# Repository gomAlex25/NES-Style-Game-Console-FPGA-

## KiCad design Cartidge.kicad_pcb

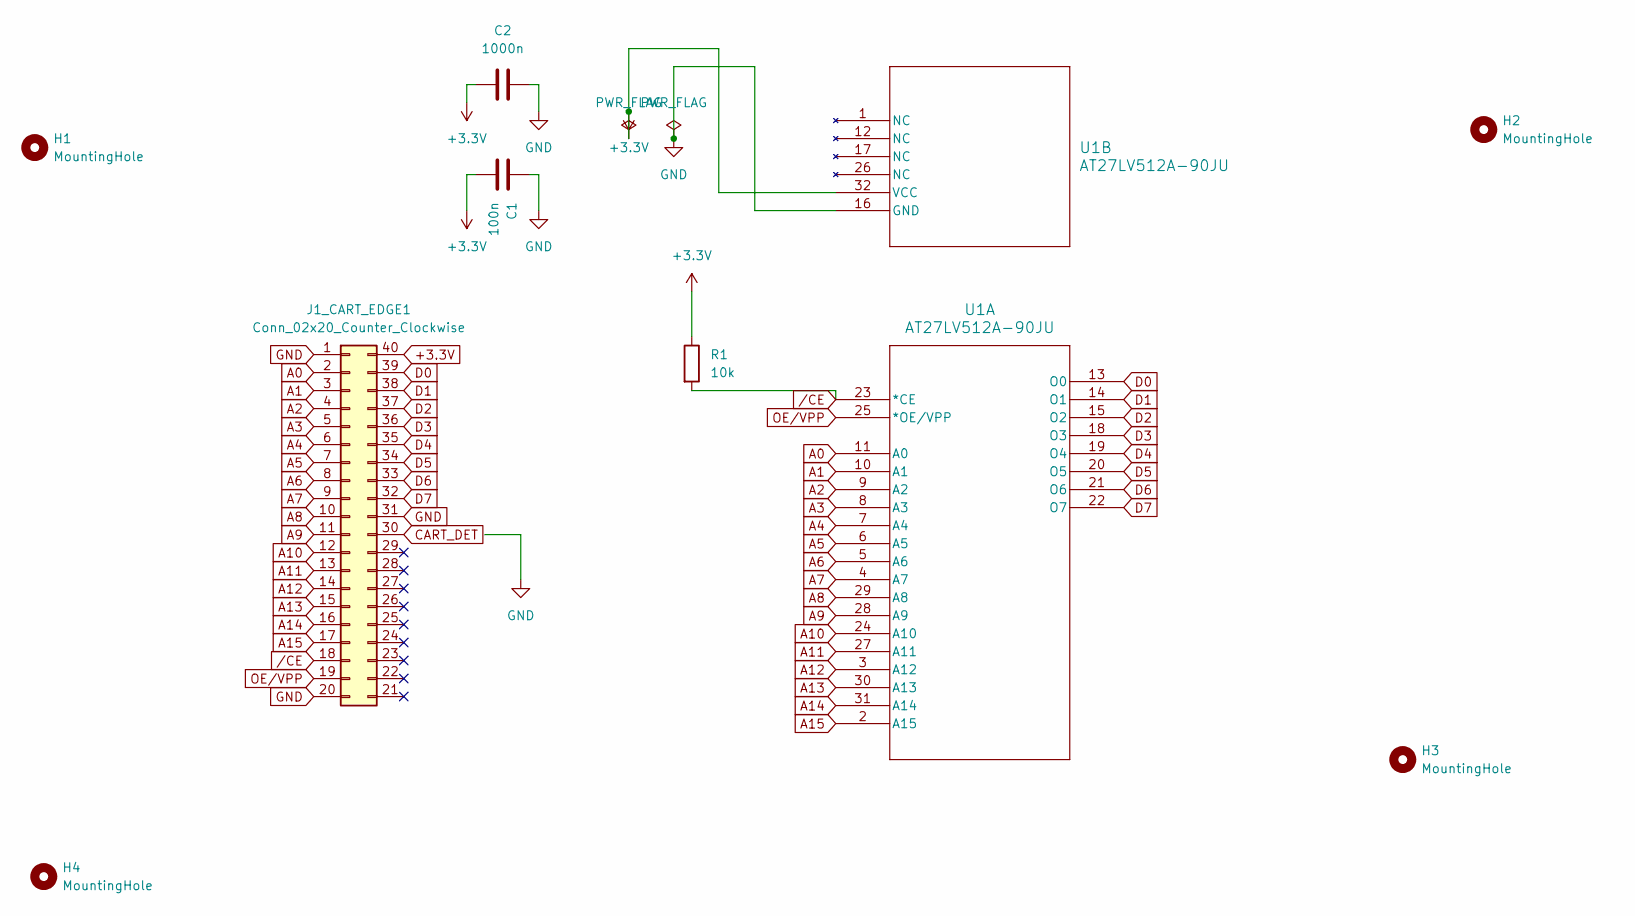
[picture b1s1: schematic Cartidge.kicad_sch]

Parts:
C1: 100n; C_Axial_L3.8mm_D2.6mm_P12.50mm_Horizontal
C2: 1000n; C_Axial_L3.8mm_D2.6mm_P12.50mm_Horizontal
H1, H2, H3, H4: MountingHole; MountingHole_2.2mm_M2_Pad_TopBottom
J1_CART_EDGE1: Conn_02x20_Counter_Clockwise; EDGEPADS_2x20_P2.54mm_W1.7_L7.0
R1: 10k; R_Axial_DIN0204_L3.6mm_D1.6mm_P5.08mm_Horizontal
U1: AT27LV512A-90JU; PLCC-32_THT-Socket

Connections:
+3.3V: C1.2, C2.1, J1_CART_EDGE1.40, R1.1, U1.32 (VCC)
A0: J1_CART_EDGE1.2, U1.11 (A0)
A1: J1_CART_EDGE1.3, U1.10 (A1)
A2: J1_CART_EDGE1.4, U1.9 (A2)
A3: J1_CART_EDGE1.5, U1.8 (A3)
A4: J1_CART_EDGE1.6, U1.7 (A4)
A5: J1_CART_EDGE1.7, U1.6 (A5)
A6: J1_CART_EDGE1.8, U1.5 (A6)
A7: J1_CART_EDGE1.9, U1.4 (A7)
A8: J1_CART_EDGE1.10, U1.29 (A8)
A9: J1_CART_EDGE1.11, U1.28 (A9)
A10: J1_CART_EDGE1.12, U1.24 (A10)
A11: J1_CART_EDGE1.13, U1.27 (A11)
A12: J1_CART_EDGE1.14, U1.3 (A12)
A13: J1_CART_EDGE1.15, U1.30 (A13)
A14: J1_CART_EDGE1.16, U1.31 (A14)
A15: J1_CART_EDGE1.17, U1.2 (A15)
CART_DET: J1_CART_EDGE1.30
D0: J1_CART_EDGE1.39, U1.13 (O0)
D1: J1_CART_EDGE1.38, U1.14 (O1)
D2: J1_CART_EDGE1.37, U1.15 (O2)
D3: J1_CART_EDGE1.36, U1.18 (O3)
D4: J1_CART_EDGE1.35, U1.19 (O4)
D5: J1_CART_EDGE1.34, U1.20 (O5)
D6: J1_CART_EDGE1.33, U1.21 (O6)
D7: J1_CART_EDGE1.32, U1.22 (O7)
GND: C1.1, C2.2, J1_CART_EDGE1.1, J1_CART_EDGE1.20, J1_CART_EDGE1.31, U1.16 (GND)
OE/VPP: J1_CART_EDGE1.19, U1.25 (*OE/VPP)
/CE: J1_CART_EDGE1.18, R1.2, U1.23 (*CE)

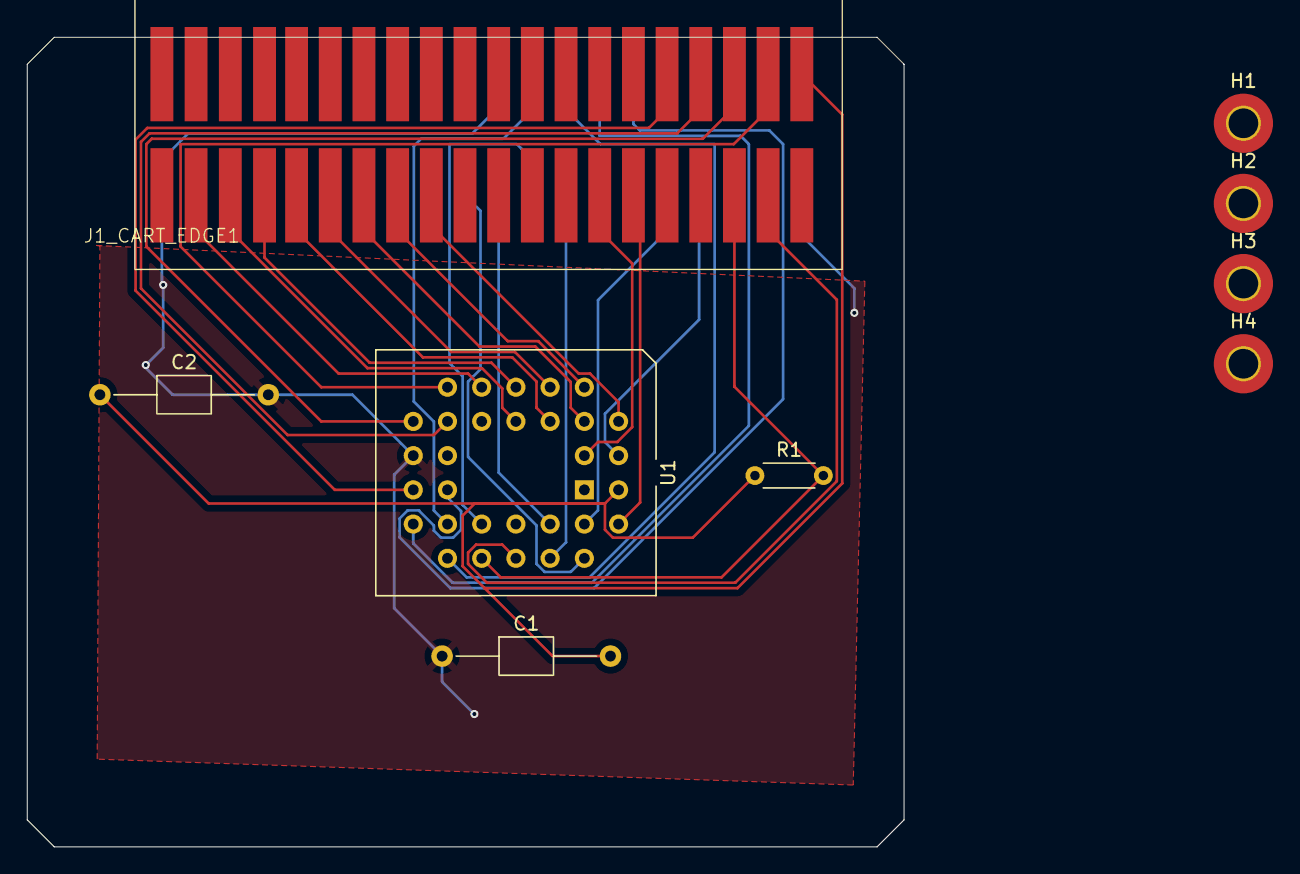
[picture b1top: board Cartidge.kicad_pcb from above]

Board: 2 copper layers, 65.1 x 60.1 mm, 9 parts (0 on the bottom side), 28 nets.

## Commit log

2026-02-20 Add product links for cartridge chip and socket
